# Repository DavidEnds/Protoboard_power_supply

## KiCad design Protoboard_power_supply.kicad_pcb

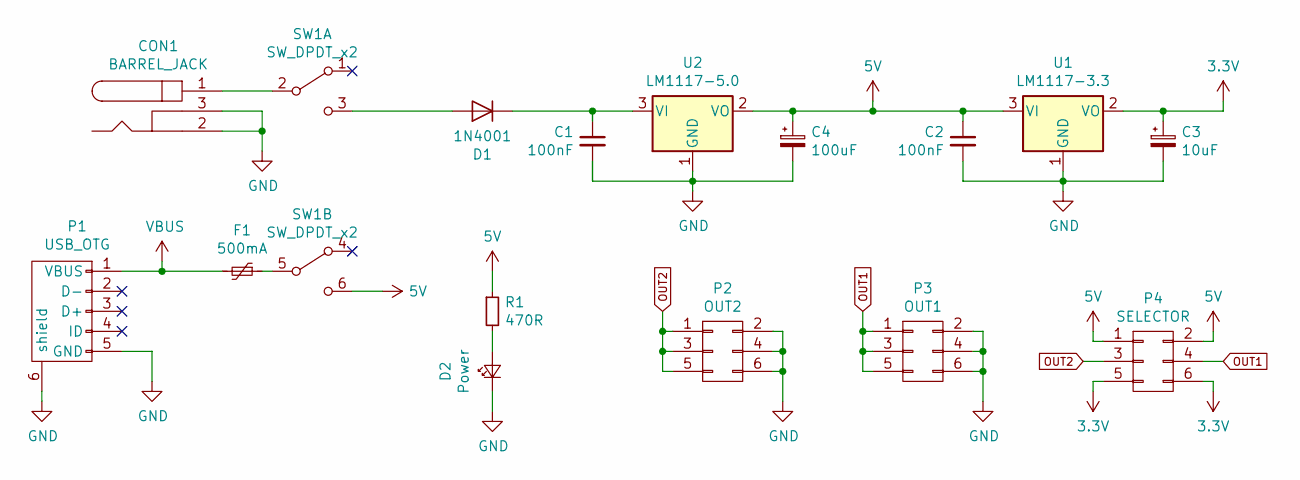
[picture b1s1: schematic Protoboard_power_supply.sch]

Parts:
C1, C2: 100nF; C_0805_HandSoldering
C3: 10uF; CP_Radial_D4.0mm_P1.50mm
C4: 100uF; CP_Radial_D6.3mm_P2.50mm
CON1: BARREL_JACK; JACK_ALIM
D1: 1N4001; D_SMA
D2: Power; LED_0805_HandSoldering
F1: 500mA; Fuse_SMD1206_Reflow
P1: USB_OTG; USB_Mini-B
P2: OUT2; Pin_Header_Straight_2x03_Pitch2.54mm
P3: OUT1; Pin_Header_Straight_2x03_Pitch2.54mm
P4: SELECTOR; Pin_Header_Straight_2x03_Pitch2.54mm
R1: 470R; R_0805_HandSoldering
SW1: SW_DPDT_x2; SW_CuK_JS202011CQN_DPDT_Straight
U1: LM1117-3.3; SOT-223
U2: LM1117-5.0; SOT-223

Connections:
3.3V: C3.1, P4.5, P4.6, U1.2 (VO)
5V: C2.1, C4.1, P4.1, P4.2, R1.1, SW1.6 (C), U1.3 (VI), U2.2 (VO)
GND: C1.2, C2.2, C3.2, C4.2, CON1.2, CON1.3, D2.1 (K), P1.5 (GND), P1.6 (shield), P2.2, P2.4, P2.6, P3.2, P3.4, P3.6, U1.1 (GND), U2.1 (GND); also elsewhere on the board
unnamed: C1.1, D1.1 (K), U2.3 (VI)
unnamed: CON1.1, SW1.2 (B)
unnamed: D1.2 (A), SW1.3 (C)
unnamed 6: D2.2 (A), R1.2; also elsewhere on the board
unnamed: F1.1, SW1.5 (B)
OUT1: P3.1, P3.3, P3.5, P4.4
OUT2: P2.1, P2.3, P2.5, P4.3
VBUS: F1.2, P1.1 (VBUS)

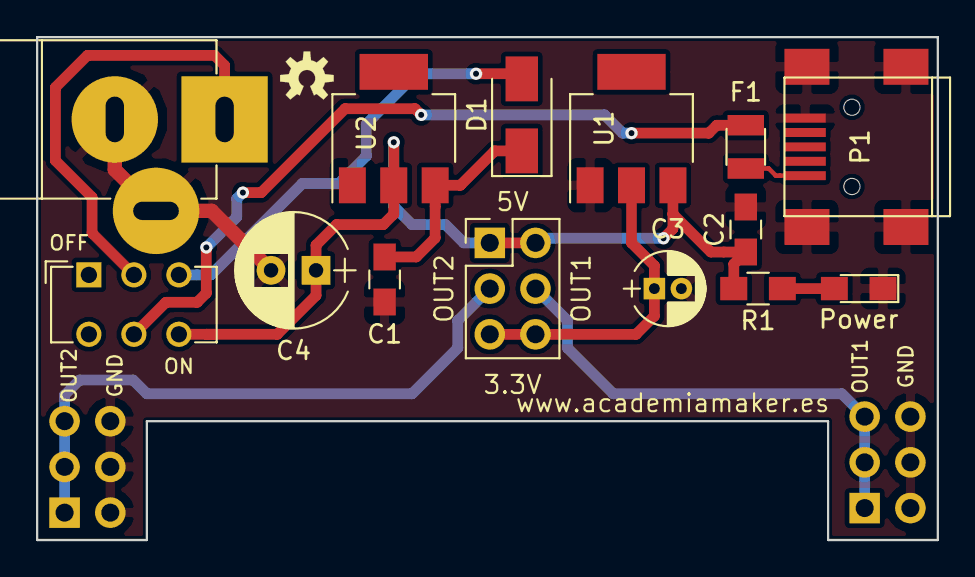
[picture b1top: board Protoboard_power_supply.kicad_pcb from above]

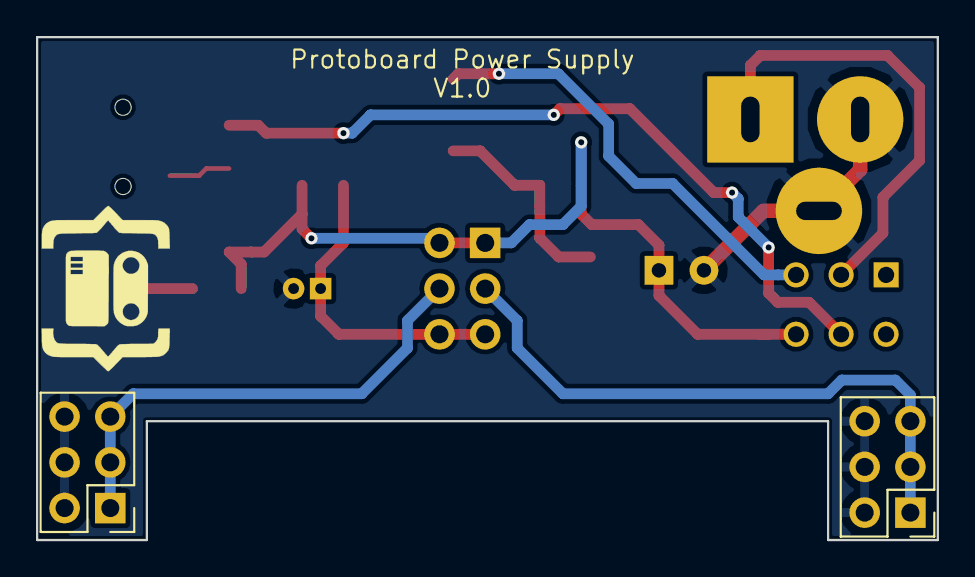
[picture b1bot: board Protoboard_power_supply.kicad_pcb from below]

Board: 2 copper layers, 50.0 x 27.9 mm, 16 parts (2 on the bottom side), 11 nets.

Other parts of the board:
Power: Power; LED_0805_HandSoldering

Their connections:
GND: Power.1; also elsewhere on the board
unnamed 6: Power.2; also elsewhere on the board

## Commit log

2018-12-09 Esquema terminado
2018-12-09 Placa terminada
2018-12-09 Mandado a fabrica
